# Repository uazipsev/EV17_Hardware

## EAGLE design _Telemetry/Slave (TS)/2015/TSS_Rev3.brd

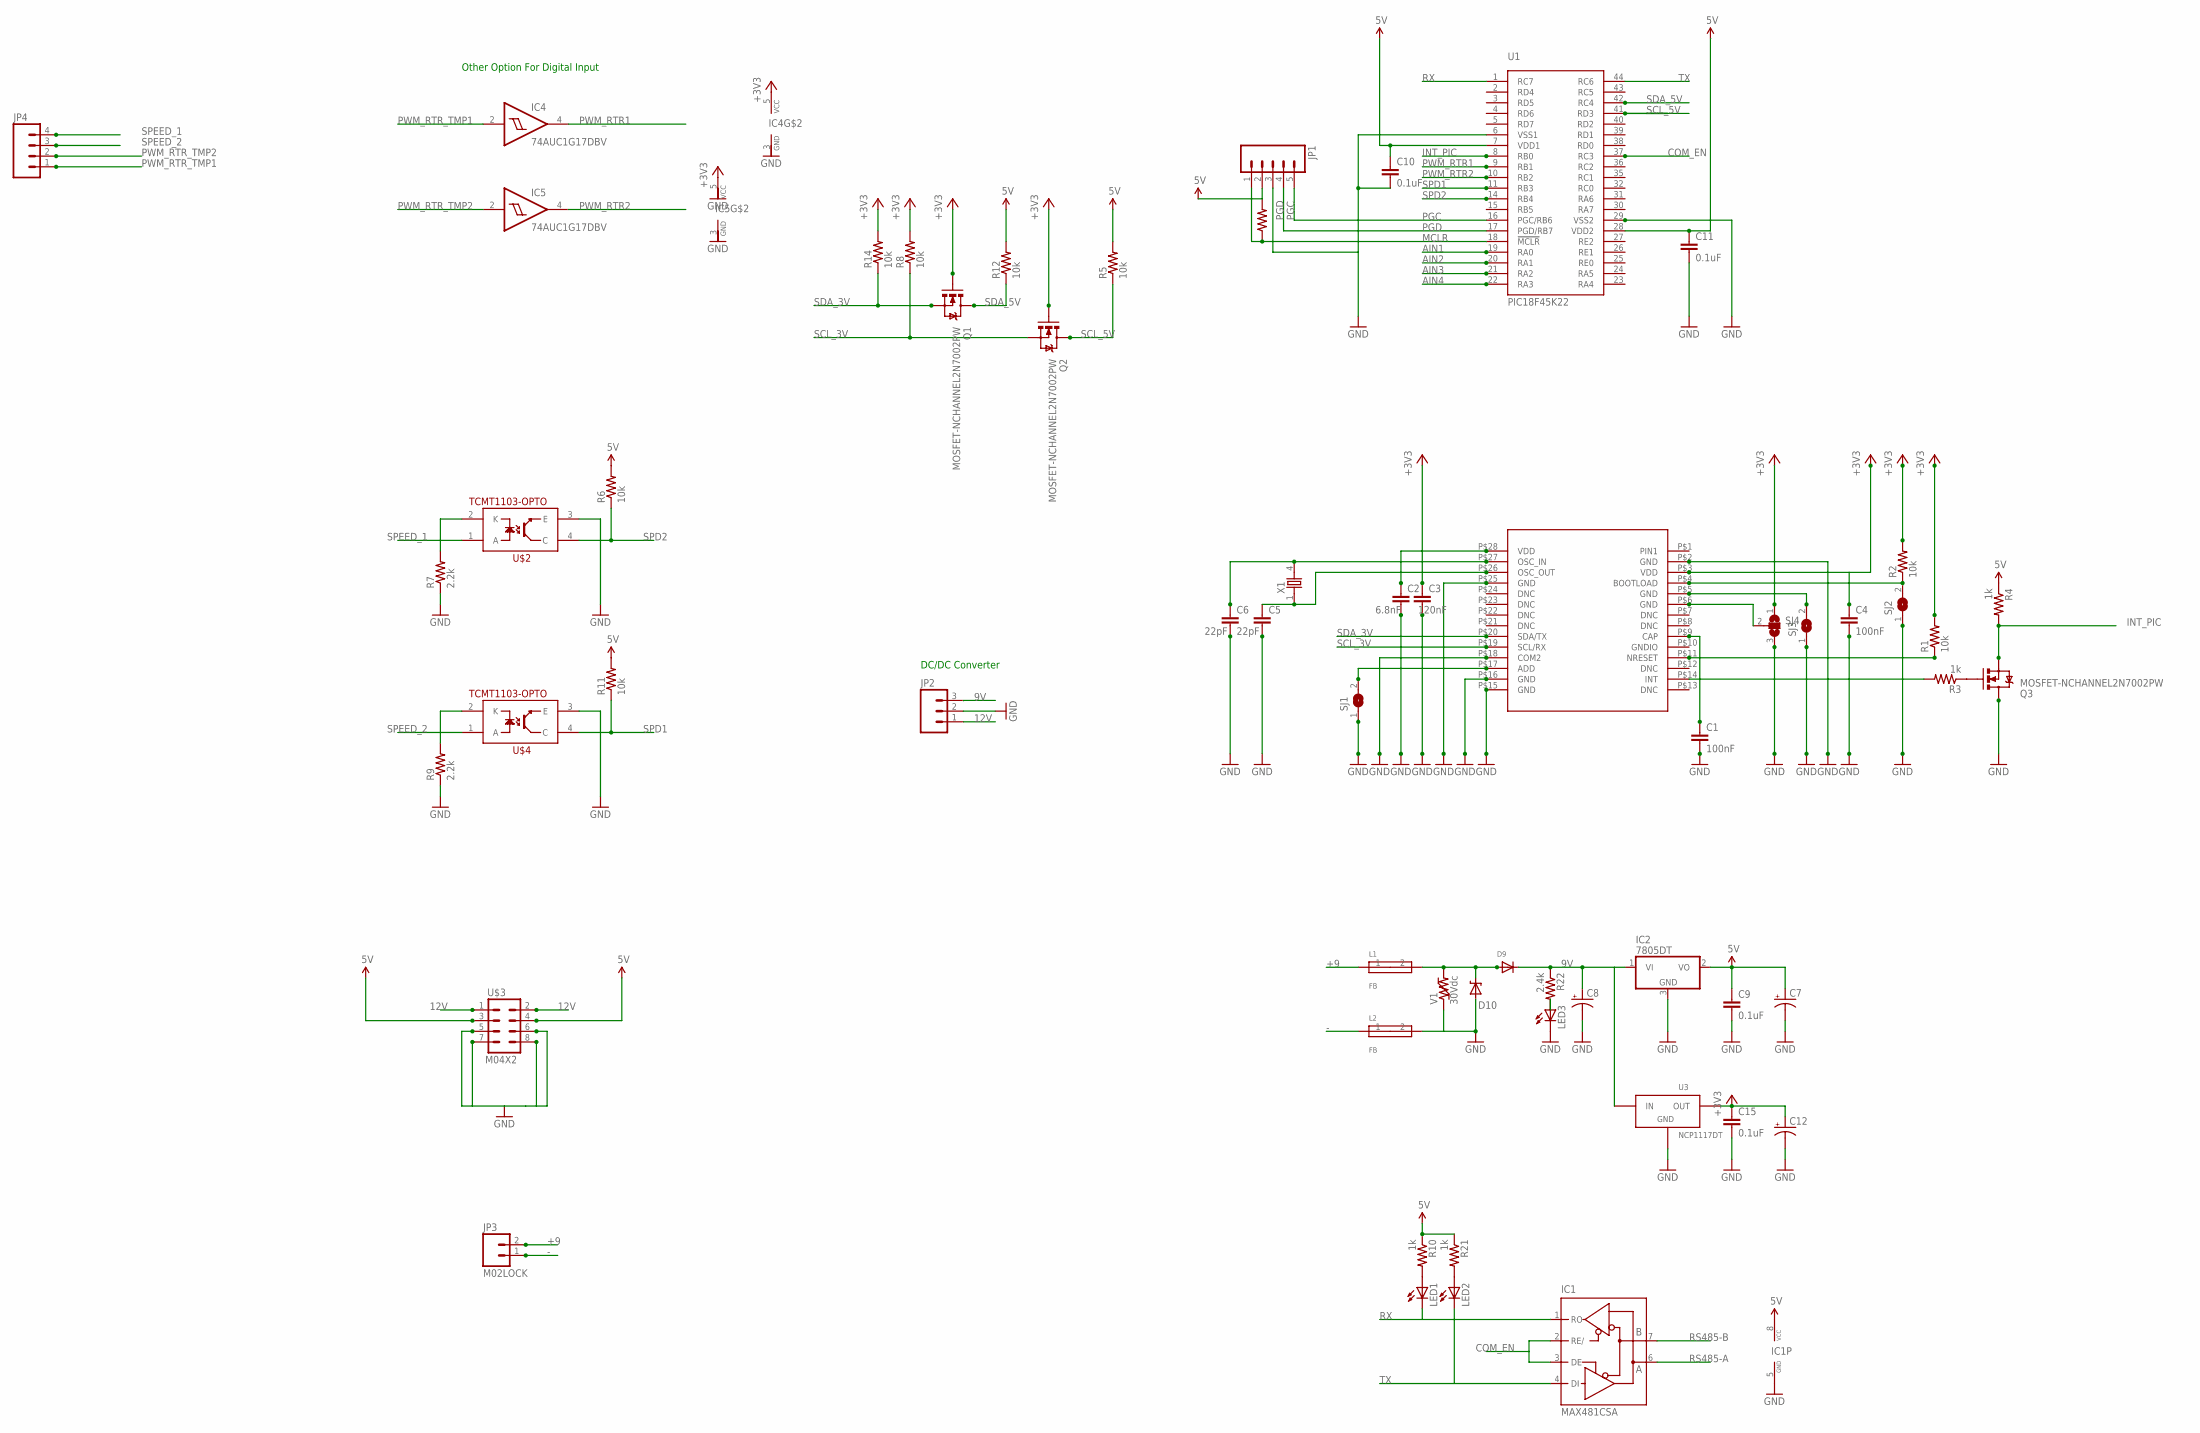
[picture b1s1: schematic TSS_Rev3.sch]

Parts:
C1, C4: 100nF; 0805
C2: 6.8nF; 0805
C3: 120nF; 0805
C5, C6: 22pF; 0805
C7, C12: CPOL-USCT3528; CT3528
C8: CAP_POL7343; EIA7343
C9, C10, C11, C15: 0.1uF; 0805
D9: DIODESOD-123; SOD-123
D10: MM5Z30; SOD-523F
IC1: MAX481CSA; SO08
IC2: 7805DT; TO252
IC4, IC5: 74AUC1G17DBV; SOT23-5
JP1: M05LOCK; 1X05_LOCK
JP2: M03PTH; 1X03
JP3: M02LOCK; 1X02_LOCK
JP4: M04LOCK; 1X04_LOCK
L1, L2: FB; 0603
LED1, LED2, LED3: LEDCHIP-LED0805; CHIP-LED0805
Q1, Q2, Q3: MOSFET-NCHANNEL2N7002PW; SOT323
R1, R2, R5, R6, R8, R11, R12, R13, R14: 10k; 0805
R3, R4, R10, R21: 1k; 0805
R7, R9: 2.2k; 0805
R22: 2.4k; 0805
SJ1, SJ2, SJ3: SJ
SJ4: SJ2W; SJ_2
U1: PIC18F45K22; TQFP-44
U2: BOSCH_IMUSURFACEMOUNT; LGA_28
U3: NCP1117DT; DPAK
U$2, U$4: TCMT1103-OPTO; SSOP-4
U$3: M04X2; 2X4
V1: 30Vdc; 0603
X1: 86SMX

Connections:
5V: C7.+, C9.1, C10.1, C11.1, IC1.8 (VCC), IC2.2 (VO), JP1.2, R4.1, R5.2, R6.2, R10.1, R11.2, R12.2, R13.2, R21.1, U1.7 (VDD1), U1.28 (VDD2), U$3.3, U$3.4
9V: C8.A (+), D9.C, IC2.1 (VI), JP2.3, R22.1, U3.3 (IN)
12V: JP2.1, U$3.1, U$3.2
+3V3: C2.1, C3.1, C4.1, C12.+, C15.1, IC4.5 (VCC), IC5.5 (VCC), Q1.1 (G), Q2.1 (G), R1.2, R2.2, R8.2, R14.2, SJ4.1, U2.P$3 (VDD), U2.P$28 (VDD), U3.2 (OUT)
+9: JP3.2, L1.1
-: JP3.1, L2.1
AIN1: U1.19 (RA0)
AIN2: U1.20 (RA1)
AIN3: U1.21 (RA2)
AIN4: U1.22 (RA3)
COM_EN: IC1.2 (RE/), IC1.3 (DE), U1.37 (RC3)
GHT: D9.A, D10.C, L1.2, V1.2
GND: C1.2, C2.2, C3.2, C4.2, C5.2, C6.2, C7.-, C8.C (-), C9.2, C10.2, C11.2, C12.-, C15.2, D10.A, IC1.5 (GND), IC2.3 (GND), IC4.3 (GND), IC5.3 (GND), JP1.3, JP2.2, L2.2, LED3.C, Q3.3 (D), R7.1, R9.1, SJ1.1, SJ2.1, SJ3.1, SJ4.3, U1.6 (VSS1), U1.29 (VSS2), U2.P$2 (GND), U2.P$15 (GND), U2.P$16 (GND), U2.P$18 (COM2), U2.P$25 (GND), U3.1 (GND), U$2.3 (E), U$3.5, U$3.6, U$3.7, U$3.8, U$4.3 (E), V1.1
INT_PIC: Q3.2 (S), R4.2, U1.8 (RB0)
MCLR: JP1.1, R13.1, U1.18 (!MCLR)
unnamed: SJ3.2, U2.P$5 (GND)
unnamed: R2.1, SJ2.2, U2.P$4 (BOOTLOAD)
unnamed: SJ4.2, U2.P$6 (GND)
unnamed: LED3.A, R22.2
unnamed: LED1.A, R10.2
unnamed: LED2.A, R21.2
unnamed: C6.1, U2.P$27 (OSC_IN), X1.4 (2)
unnamed: C5.1, U2.P$26 (OSC_OUT), X1.1
unnamed: R7.2, U$2.2 (K)
unnamed: SJ1.2, U2.P$17 (ADD)
unnamed: R9.2, U$4.2 (K)
unnamed: R3.2, U2.P$14 (INT)
unnamed: C1.1, U2.P$9 (CAP)
unnamed: R1.1, U2.P$11 (NRESET)
unnamed: Q3.1 (G), R3.1
PGC: JP1.5, U1.16 (PGC/RB6)
PGD: JP1.4, U1.17 (PGD/RB7)
PWM_RTR1: IC4.4 (O), U1.9 (RB1)
PWM_RTR2: IC5.4 (O), U1.10 (RB2)
PWM_RTR_TMP1: IC4.2 (I), JP4.1
PWM_RTR_TMP2: IC5.2 (I), JP4.2
RS485-A: IC1.6 (A)
RS485-B: IC1.7 (B)
RX: IC1.1 (RO), LED1.C, U1.1 (RC7)
SCL_3V: Q2.2 (S), R8.1, U2.P$19 (SCL/RX)
SCL_5V: Q2.3 (D), R5.1, U1.41 (RD3)
SDA_3V: Q1.2 (S), R14.1, U2.P$20 (SDA/TX)
SDA_5V: Q1.3 (D), R12.1, U1.42 (RC4)
SPD1: R11.1, U1.11 (RB3), U$4.4 (C)
SPD2: R6.1, U1.14 (RB4), U$2.4 (C)
SPEED_1: JP4.4, U$2.1 (A)
SPEED_2: JP4.3, U$4.1 (A)
TX: IC1.4 (DI), LED2.C, U1.44 (RC6)

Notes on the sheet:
DC/DC Converter
Other Option For Digital Input

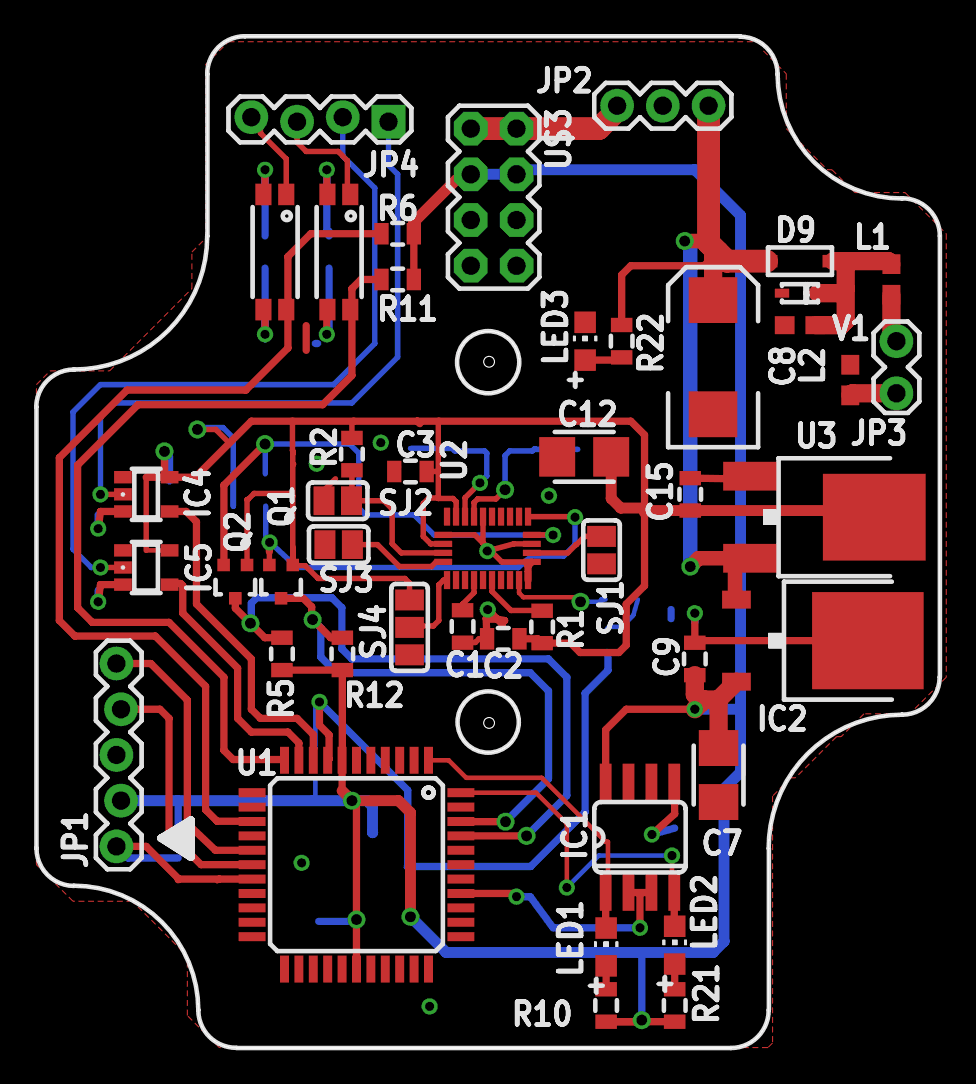
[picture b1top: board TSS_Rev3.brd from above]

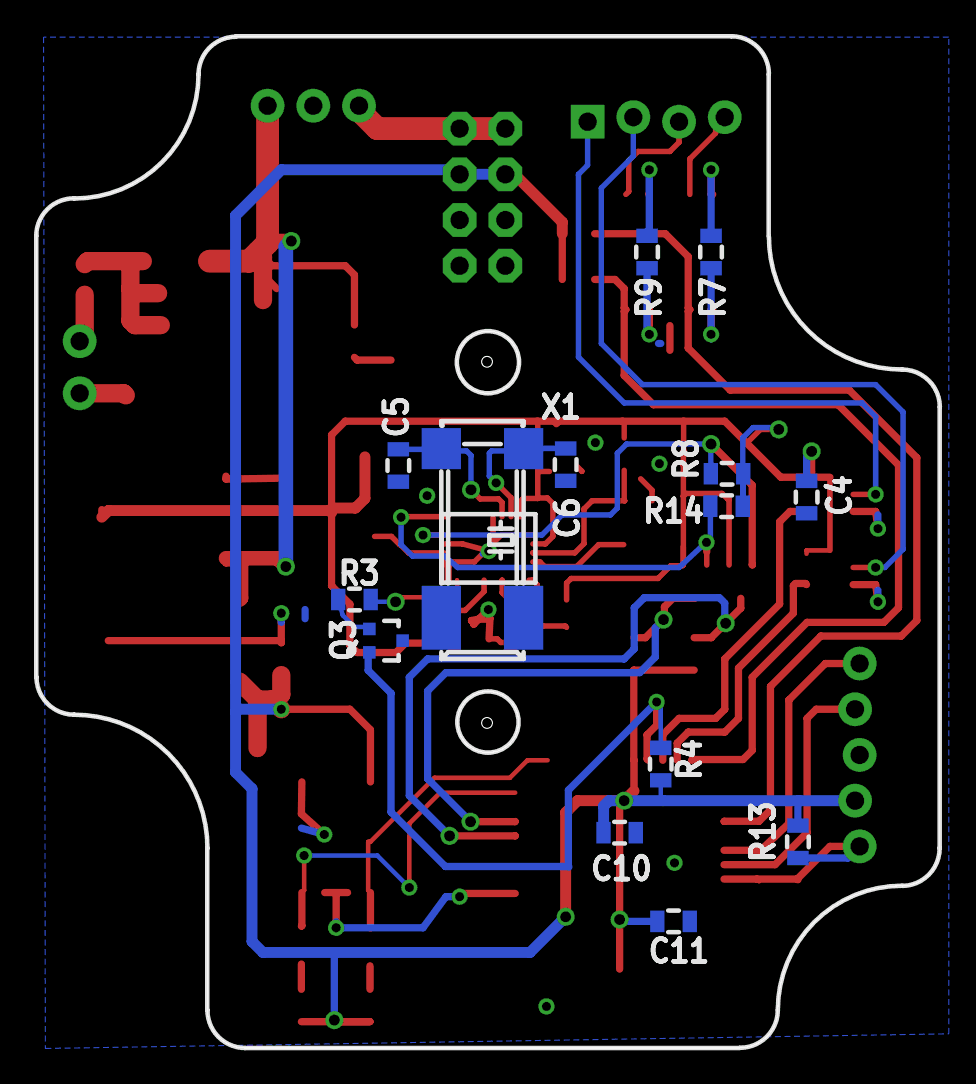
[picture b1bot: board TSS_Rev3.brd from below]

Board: 2 copper layers, 50.2 x 56.2 mm, 59 parts (14 on the bottom side), 42 nets.

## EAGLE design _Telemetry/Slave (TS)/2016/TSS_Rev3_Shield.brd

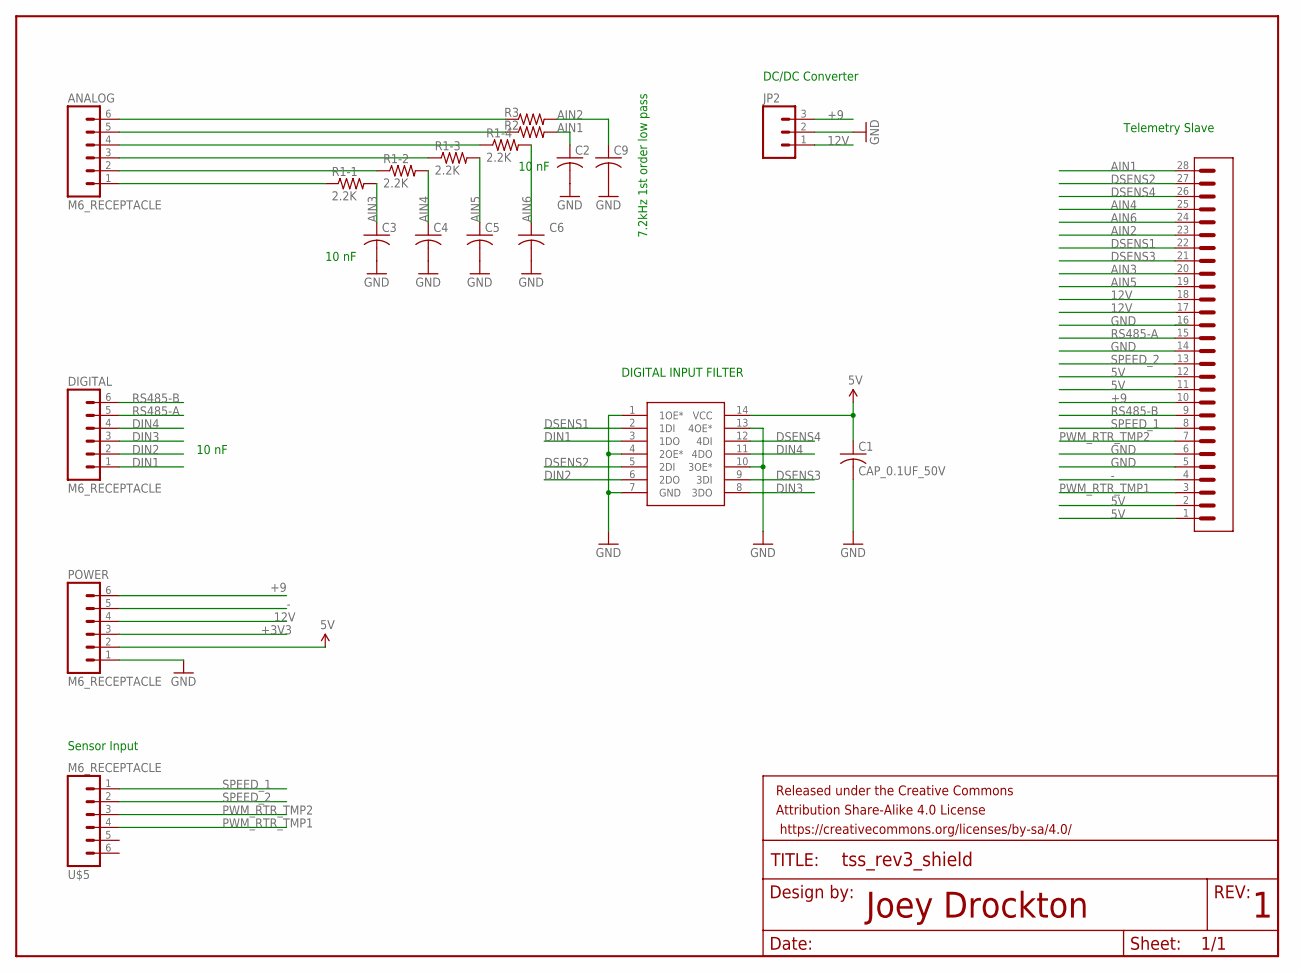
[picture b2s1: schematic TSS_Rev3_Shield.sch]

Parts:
ANALOG: M6_RECEPTACLE; 6X.1
C1: CAP_0.1UF_50V; 0603
C2, C3, C4, C5, C6, C9: CAP_10NF_50V; 0603
DIGITAL: M6_RECEPTACLE; 6X.1
FRAME1: FRAME-LETTERNO_PACKAGE; DUMMY
JP2: M03PTH; 1X03
POWER: M6_RECEPTACLE; 6X.1
R1: 2.2K; MNR14
R2, R3: RES_2.2K_1%; 0603
U$1: 1-207216-6
U$2: 74HC125S14-13; SO-14
U$5: M6_RECEPTACLE; 6X.1

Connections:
5V: C1.1 (+), POWER.2, U$1.1, U$1.2, U$1.11, U$1.12, U$2.14 (VCC)
12V: JP2.1, POWER.4, U$1.17, U$1.18
+3V3: POWER.3
+9: JP2.3, POWER.6, U$1.10
-: POWER.5, U$1.4
AIN1: C2.1 (+), R2.2, U$1.28
AIN2: C9.1 (+), R3.2, U$1.23
AIN3: C3.1 (+), R1.8 (2), U$1.20
AIN4: C4.1 (+), R1.7 (2), U$1.25
AIN5: C5.1 (+), R1.6 (2), U$1.19
AIN6: C6.1 (+), R1.5 (2), U$1.24
DIN1: DIGITAL.1, U$2.3 (1DO)
DIN2: DIGITAL.2, U$2.6 (2DO)
DIN3: DIGITAL.3, U$2.8 (3DO)
DIN4: DIGITAL.4, U$2.11 (4DO)
DSENS1: U$1.22, U$2.2 (1DI)
DSENS2: U$1.27, U$2.5 (2DI)
DSENS3: U$1.21, U$2.9 (3DI)
DSENS4: U$1.26, U$2.12 (4DI)
GND: C1.2 (-), C2.2 (-), C3.2 (-), C4.2 (-), C5.2 (-), C6.2 (-), C9.2 (-), JP2.2, POWER.1, U$1.5, U$1.6, U$1.14, U$1.16, U$2.1 (1OE*), U$2.4 (2OE*), U$2.7 (GND), U$2.10 (3OE*), U$2.13 (4OE*)
unnamed: ANALOG.6, R3.1
unnamed: ANALOG.5, R2.1
unnamed: ANALOG.4, R1.4 (1)
unnamed: ANALOG.3, R1.3 (1)
unnamed: ANALOG.2, R1.2 (1)
unnamed: ANALOG.1, R1.1
PWM_RTR_TMP1: U$1.3, U$5.4
PWM_RTR_TMP2: U$1.7, U$5.3
RS485-A: DIGITAL.5, U$1.15
RS485-B: DIGITAL.6, U$1.9
SPEED_1: U$1.8, U$5.1
SPEED_2: U$1.13, U$5.2

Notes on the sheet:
Sensor Input
DC/DC Converter
7.2kHz 1st order low pass
10 nF
DIGITAL INPUT FILTER
Joey Drockton
Telemetry Slave

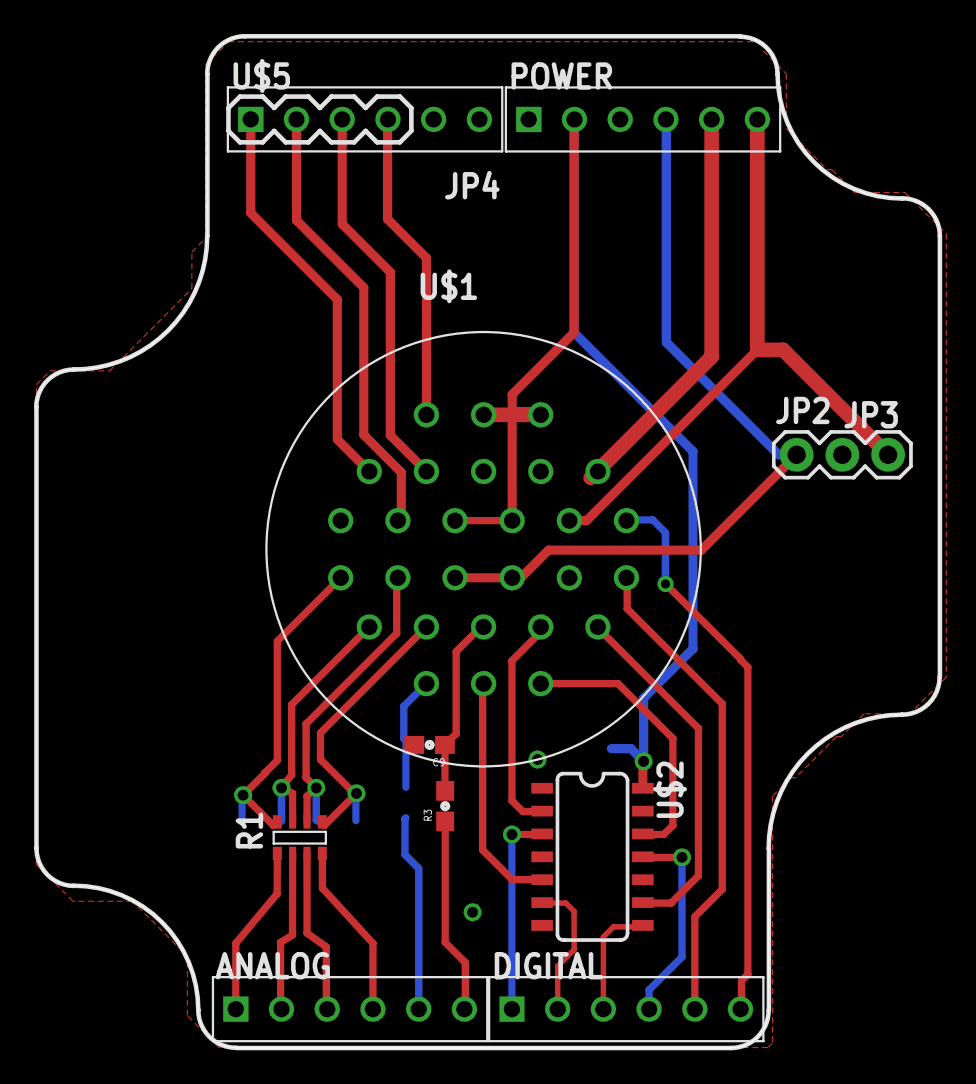
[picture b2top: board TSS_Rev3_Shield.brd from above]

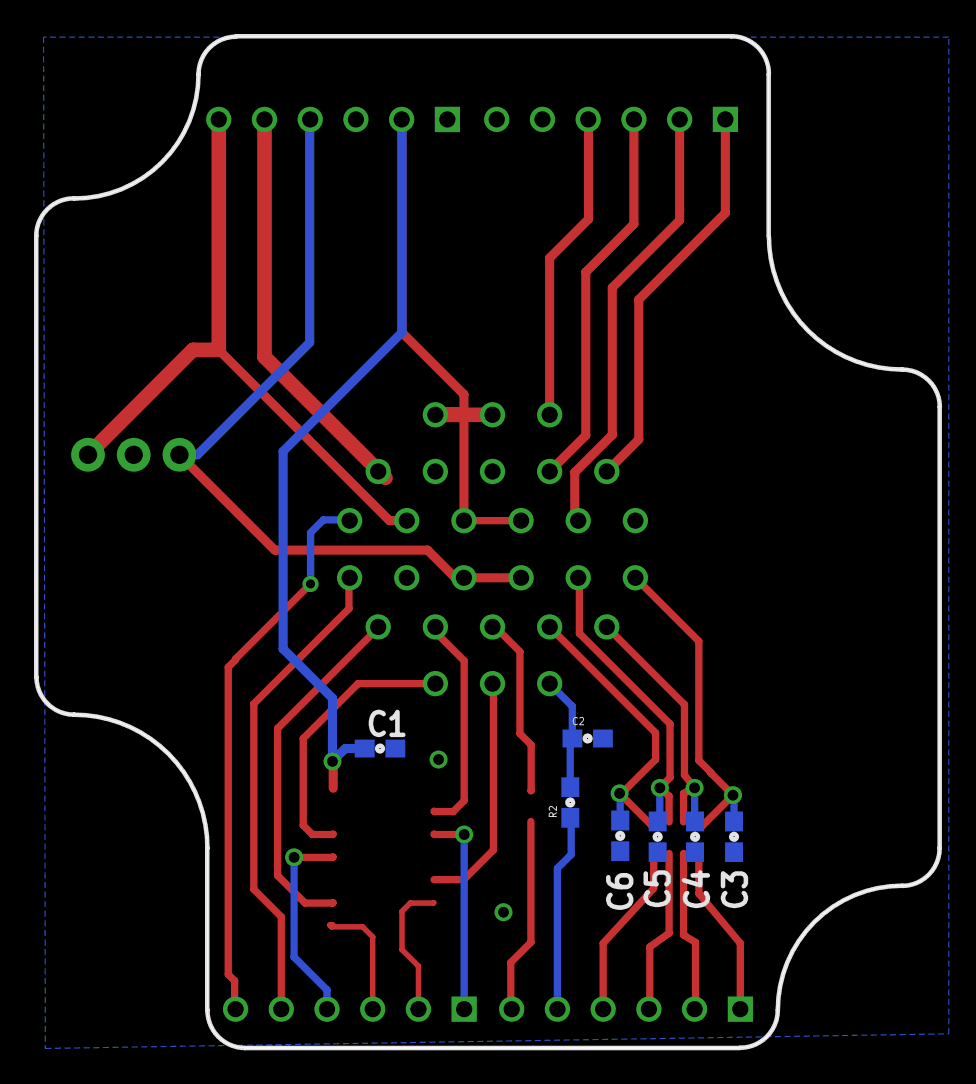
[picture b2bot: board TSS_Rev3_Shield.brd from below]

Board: 2 copper layers, 50.2 x 56.2 mm, 18 parts (7 on the bottom side), 31 nets.

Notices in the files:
parts and their libraries:
SparkFun-Passives: Licensing: Creative Commons ShareAlike 4.0 International - https://creativecommons.org/licenses/by-sa/4.0
SparkFun-Aesthetics: Released under the Creative Commons Attribution Share-Alike 4.0 License
SparkFun-Aesthetics: https://creativecommons.org/licenses/by-sa/4.0
